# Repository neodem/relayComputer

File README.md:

# relayComputer
Files Relating to my Relay Based Computer

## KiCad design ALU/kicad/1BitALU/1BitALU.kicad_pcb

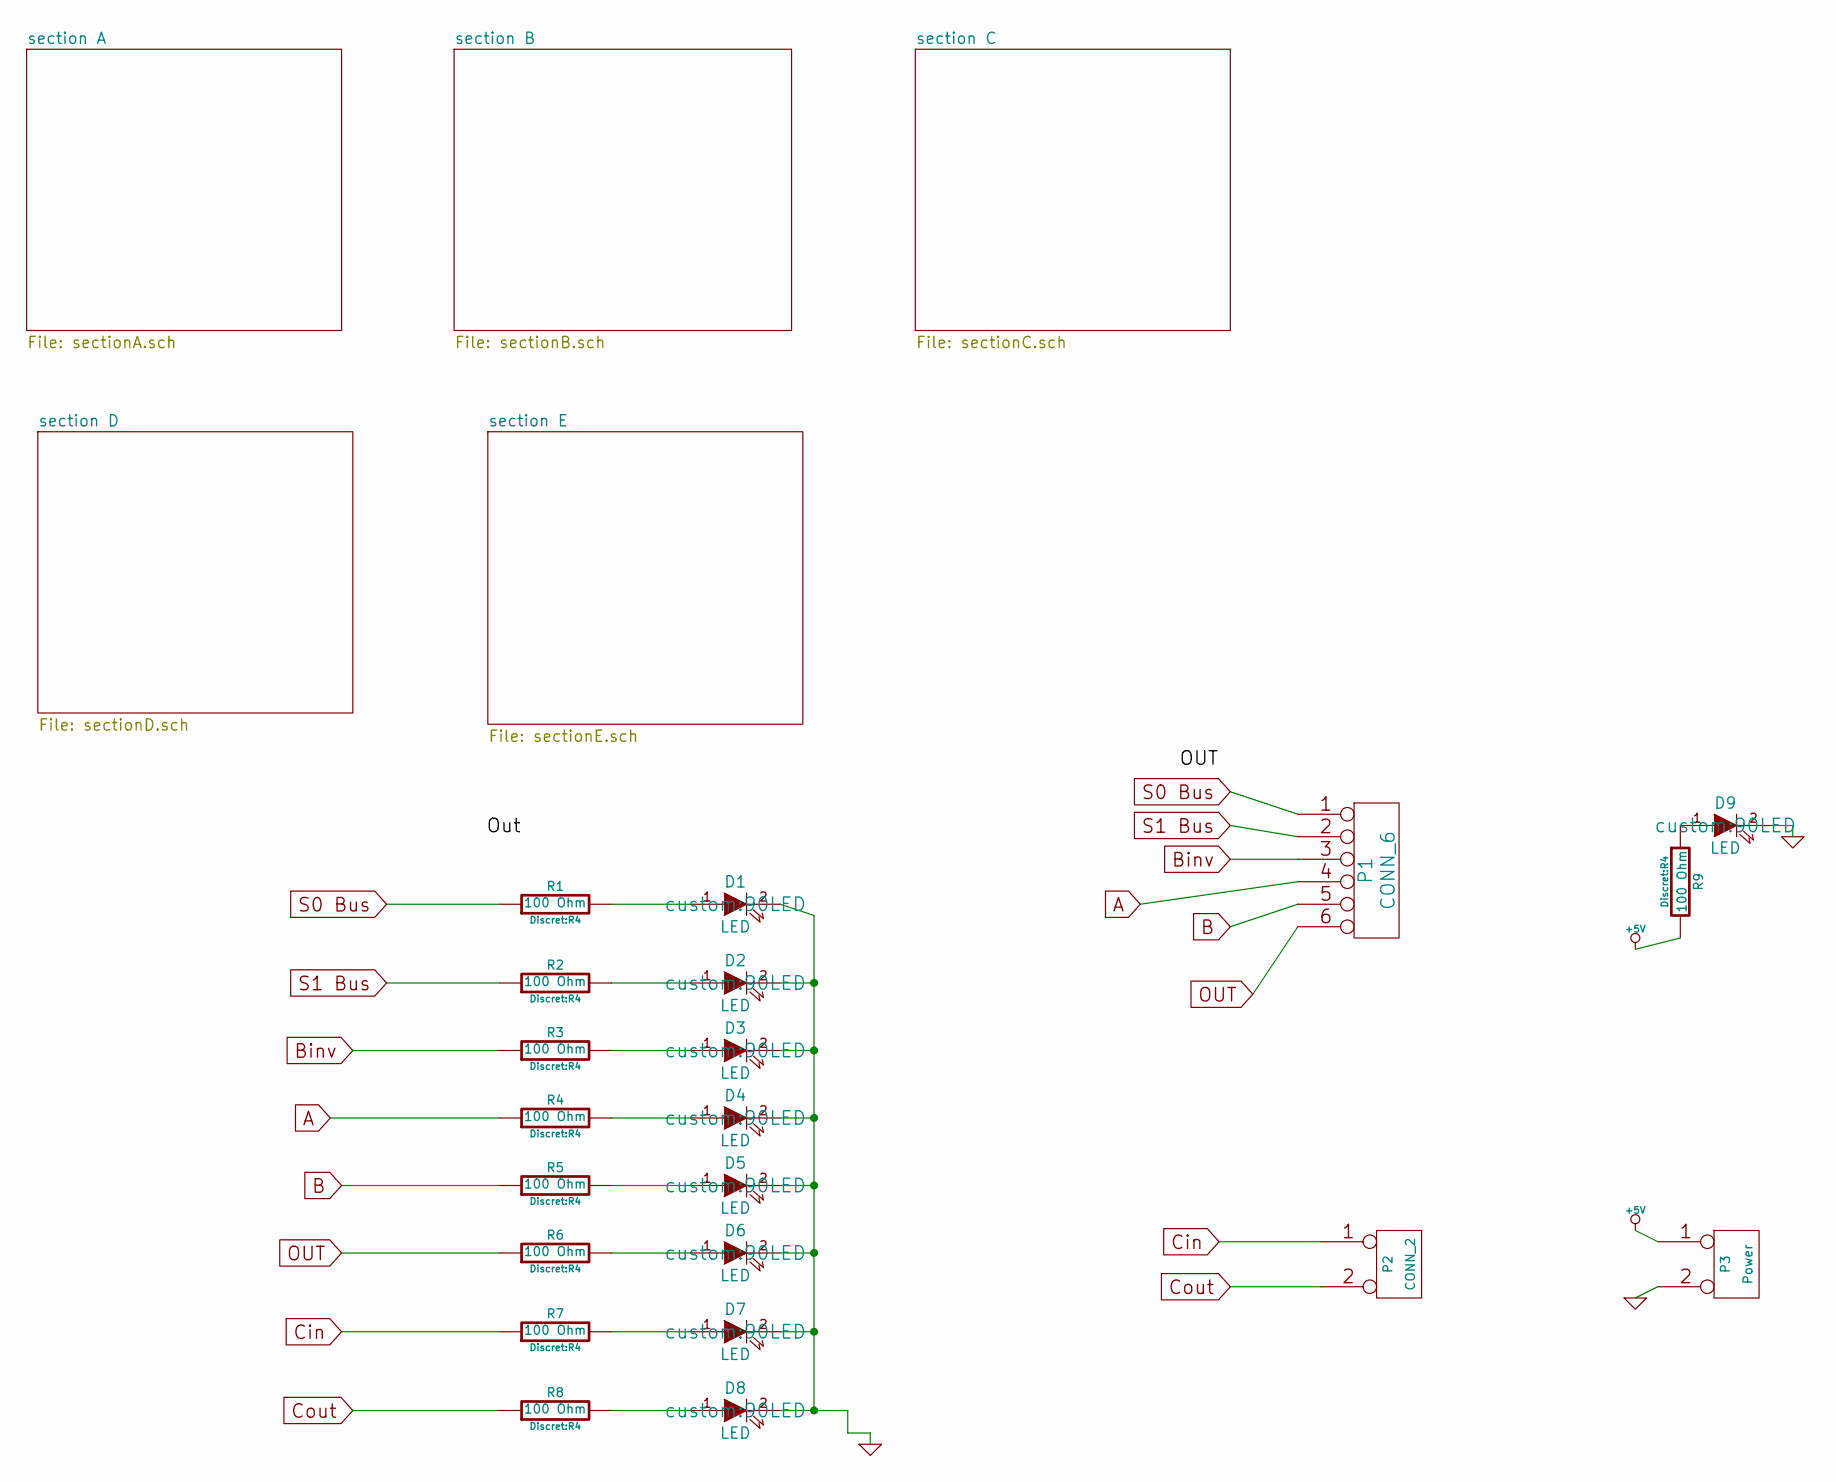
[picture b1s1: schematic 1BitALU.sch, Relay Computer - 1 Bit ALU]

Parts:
D1, D2, D3, D4, D5, D6, D7, D8, D9: LED; 90LED
P1: CONN_6; Socket_Strip_Angled_1x06
P2: CONN_2; Socket_Strip_Angled_1x02
P3: Power; Socket_Strip_Angled_1x02
R1, R2, R3, R4, R5, R6, R7, R8, R9: 100 Ohm; R4

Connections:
+5V: P3.1, R9.2; also elsewhere on the board
A: P1.4, R4.1; also elsewhere on the board
B: P1.5, R5.1; also elsewhere on the board
Binv: P1.3, R3.1; also elsewhere on the board
Cin: P2.1, R7.1; also elsewhere on the board
Cout: P2.2 (PM), R8.1; also elsewhere on the board
GND: D1.2 (K), D2.2 (K), D3.2 (K), D4.2 (K), D5.2 (K), D6.2 (K), D7.2 (K), D8.2 (K), D9.2 (K), P3.2 (PM); also elsewhere on the board
unnamed: D1.1 (A), R1.2
unnamed: D2.1 (A), R2.2
unnamed: D3.1 (A), R3.2
unnamed: D4.1 (A), R4.2
unnamed: D5.1 (A), R5.2
unnamed: D6.1 (A), R6.2
unnamed: D7.1 (A), R7.2
unnamed: D8.1 (A), R8.2
unnamed: D9.1 (A), R9.1
OUT: P1.6, R6.1; also elsewhere on the board
S0 Bus: P1.1, R1.1; also elsewhere on the board
S1 Bus: P1.2, R2.1; also elsewhere on the board

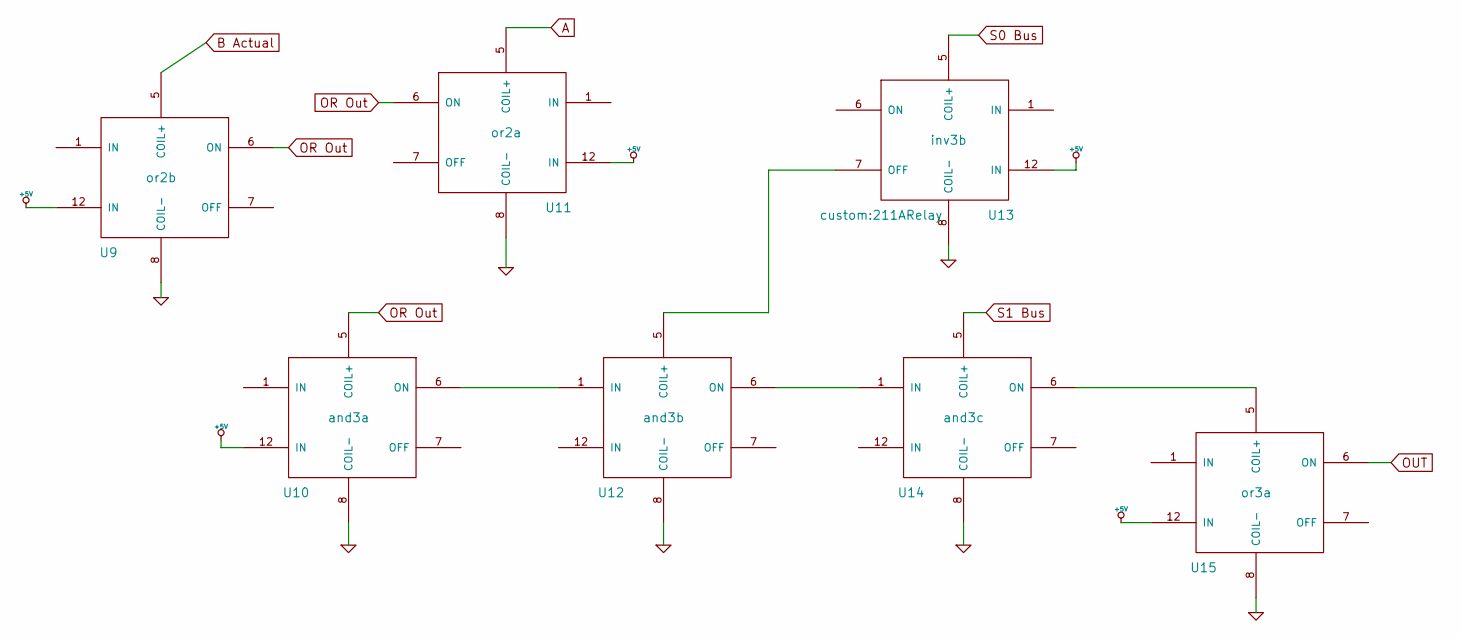
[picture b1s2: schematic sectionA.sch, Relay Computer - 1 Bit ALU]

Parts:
U9: or2b; 211ARelay
U10: and3a; 211ARelay
U11: or2a; 211ARelay
U12: and3b; 211ARelay
U13: inv3b; 211ARelay
U14: and3c; 211ARelay
U15: or3a; 211ARelay

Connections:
+5V: U9.12 (IN), U10.12 (IN), U11.12 (IN), U13.12 (IN), U15.12 (IN); also elsewhere on the board
A: U11.5 (COIL+); also elsewhere on the board
B Actual: U9.5 (COIL+); also elsewhere on the board
GND: U9.8 (COIL-), U10.8 (COIL-), U11.8 (COIL-), U12.8 (COIL-), U13.8 (COIL-), U14.8 (COIL-), U15.8 (COIL-); also elsewhere on the board
unnamed: U10.6 (ON), U12.1 (IN)
unnamed: U12.5 (COIL+), U13.7 (OFF)
unnamed: U12.6 (ON), U14.1 (IN)
unnamed: U14.6 (ON), U15.5 (COIL+)
OR Out: U9.6 (ON), U10.5 (COIL+), U11.6 (ON)
OUT: U15.6 (ON); also elsewhere on the board
S0 Bus: U13.5 (COIL+); also elsewhere on the board
S1 Bus: U14.5 (COIL+); also elsewhere on the board

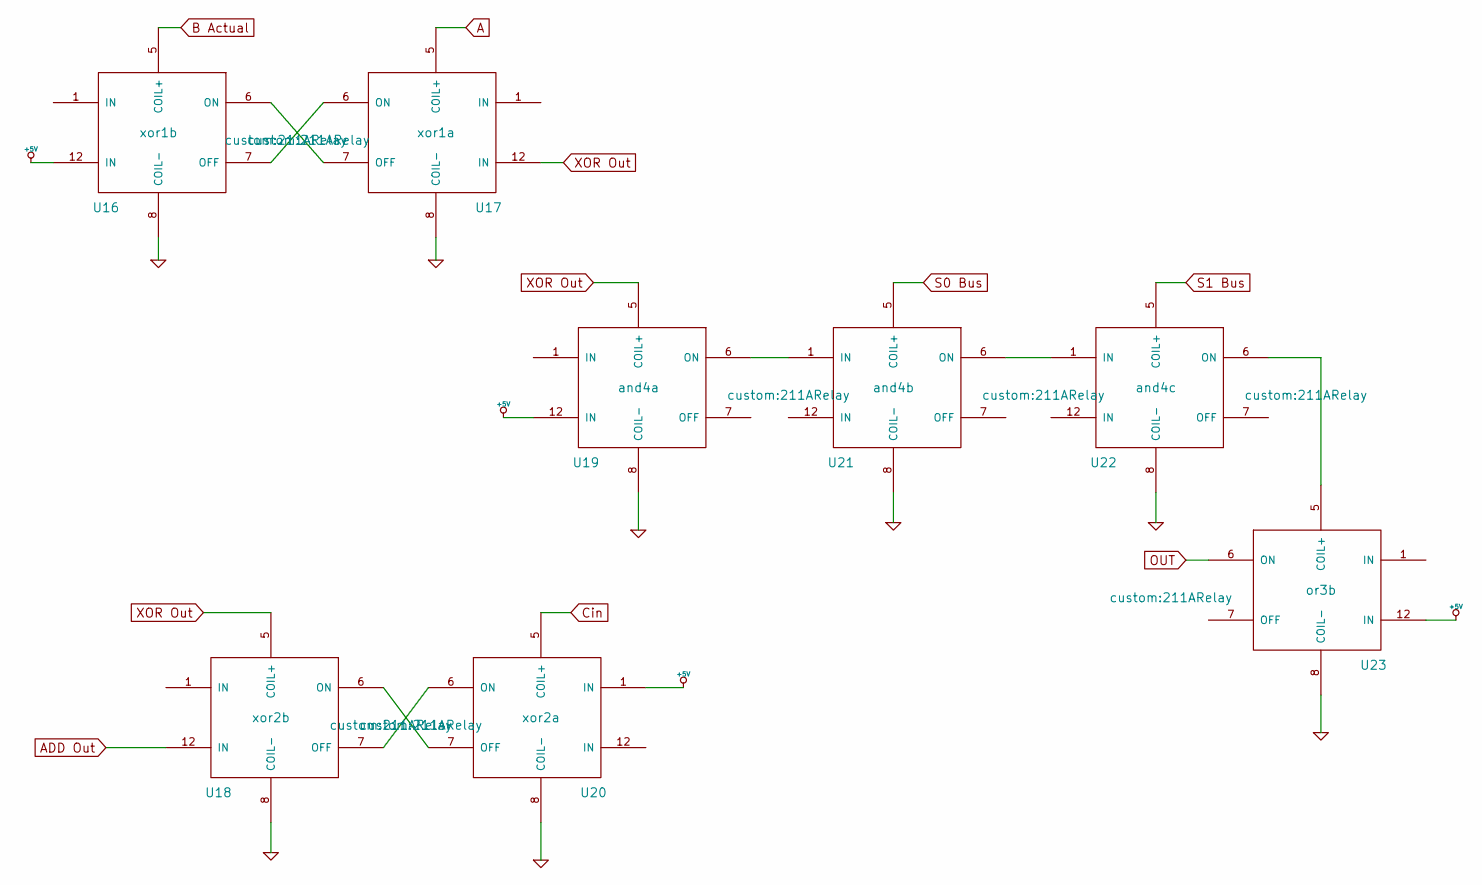
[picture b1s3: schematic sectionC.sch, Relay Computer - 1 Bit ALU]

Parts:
U16: xor1b; 211ARelay
U17: xor1a; 211ARelay
U18: xor2b; 211ARelay
U19: and4a; 211ARelay
U20: xor2a; 211ARelay
U21: and4b; 211ARelay
U22: and4c; 211ARelay
U23: or3b; 211ARelay

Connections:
+5V: U16.12 (IN), U19.12 (IN), U20.1 (IN), U23.12 (IN); also elsewhere on the board
A: U17.5 (COIL+); also elsewhere on the board
ADD Out: U18.12 (IN); also elsewhere on the board
B Actual: U16.5 (COIL+); also elsewhere on the board
Cin: U20.5 (COIL+); also elsewhere on the board
GND: U16.8 (COIL-), U17.8 (COIL-), U18.8 (COIL-), U19.8 (COIL-), U20.8 (COIL-), U21.8 (COIL-), U22.8 (COIL-), U23.8 (COIL-); also elsewhere on the board
unnamed: U16.6 (ON), U17.7 (OFF)
unnamed: U16.7 (OFF), U17.6 (ON)
unnamed: U18.6 (ON), U20.7 (OFF)
unnamed: U18.7 (OFF), U20.6 (ON)
unnamed: U19.6 (ON), U21.1 (IN)
unnamed: U21.6 (ON), U22.1 (IN)
unnamed: U22.6 (ON), U23.5 (COIL+)
OUT: U23.6 (ON); also elsewhere on the board
S0 Bus: U21.5 (COIL+); also elsewhere on the board
S1 Bus: U22.5 (COIL+); also elsewhere on the board
XOR Out: U17.12 (IN), U18.5 (COIL+), U19.5 (COIL+); also elsewhere on the board

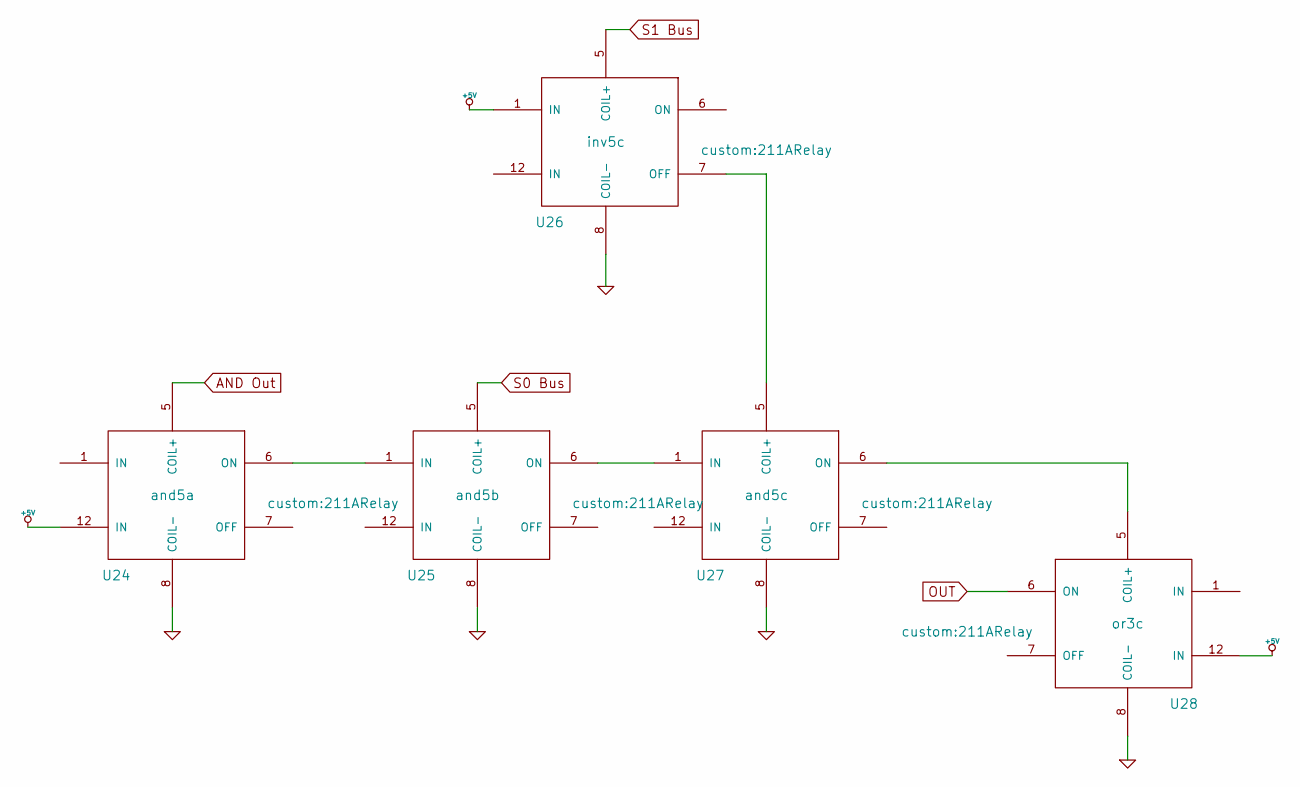
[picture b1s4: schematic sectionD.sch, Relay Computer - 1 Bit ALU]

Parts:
U24: and5a; 211ARelay
U25: and5b; 211ARelay
U26: inv5c; 211ARelay
U27: and5c; 211ARelay
U28: or3c; 211ARelay

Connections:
+5V: U24.12 (IN), U26.1 (IN), U28.12 (IN); also elsewhere on the board
AND Out: U24.5 (COIL+); also elsewhere on the board
GND: U24.8 (COIL-), U25.8 (COIL-), U26.8 (COIL-), U27.8 (COIL-), U28.8 (COIL-); also elsewhere on the board
unnamed: U24.6 (ON), U25.1 (IN)
unnamed: U25.6 (ON), U27.1 (IN)
unnamed: U26.7 (OFF), U27.5 (COIL+)
unnamed: U27.6 (ON), U28.5 (COIL+)
OUT: U28.6 (ON); also elsewhere on the board
S0 Bus: U25.5 (COIL+); also elsewhere on the board
S1 Bus: U26.5 (COIL+); also elsewhere on the board

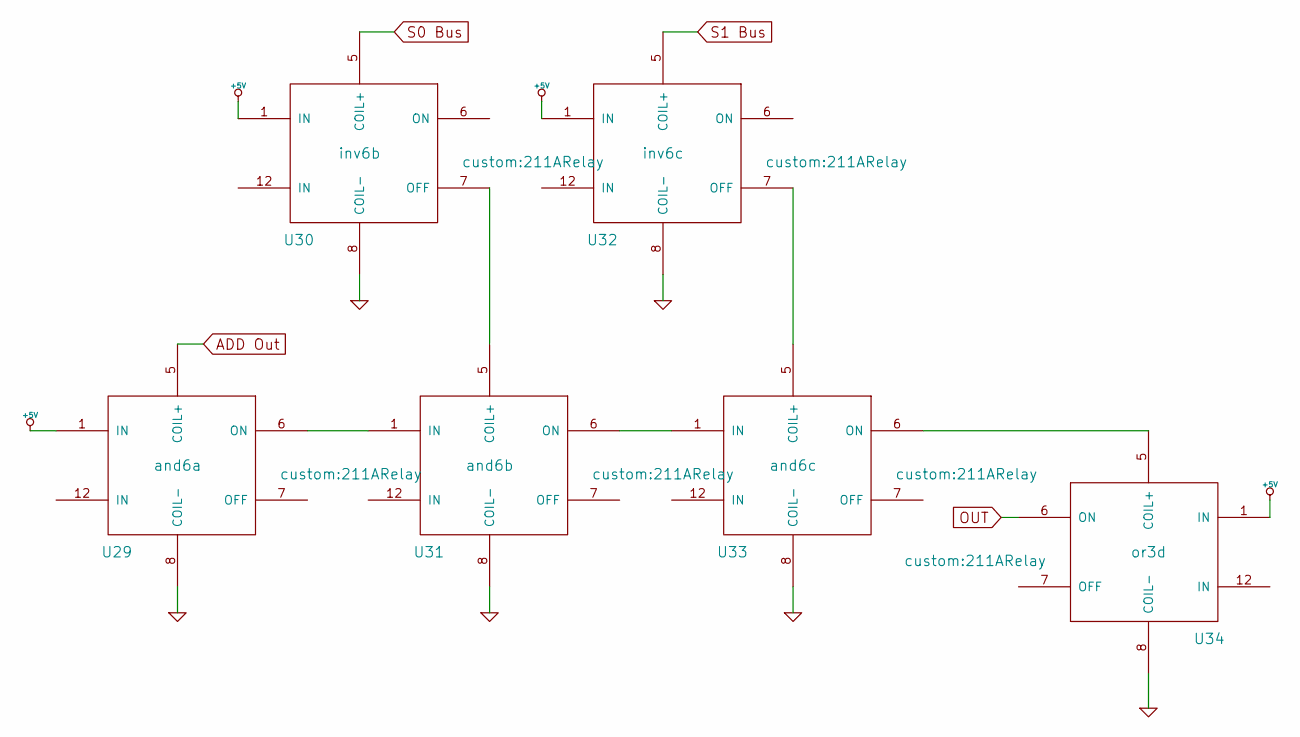
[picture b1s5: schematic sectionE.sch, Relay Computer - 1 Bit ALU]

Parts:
U29: and6a; 211ARelay
U30: inv6b; 211ARelay
U31: and6b; 211ARelay
U32: inv6c; 211ARelay
U33: and6c; 211ARelay
U34: or3d; 211ARelay

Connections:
+5V: U29.1 (IN), U30.1 (IN), U32.1 (IN), U34.1 (IN); also elsewhere on the board
ADD Out: U29.5 (COIL+); also elsewhere on the board
GND: U29.8 (COIL-), U30.8 (COIL-), U31.8 (COIL-), U32.8 (COIL-), U33.8 (COIL-), U34.8 (COIL-); also elsewhere on the board
unnamed: U29.6 (ON), U31.1 (IN)
unnamed: U30.7 (OFF), U31.5 (COIL+)
unnamed: U31.6 (ON), U33.1 (IN)
unnamed: U32.7 (OFF), U33.5 (COIL+)
unnamed: U33.6 (ON), U34.5 (COIL+)
OUT: U34.6 (ON); also elsewhere on the board
S0 Bus: U30.5 (COIL+); also elsewhere on the board
S1 Bus: U32.5 (COIL+); also elsewhere on the board

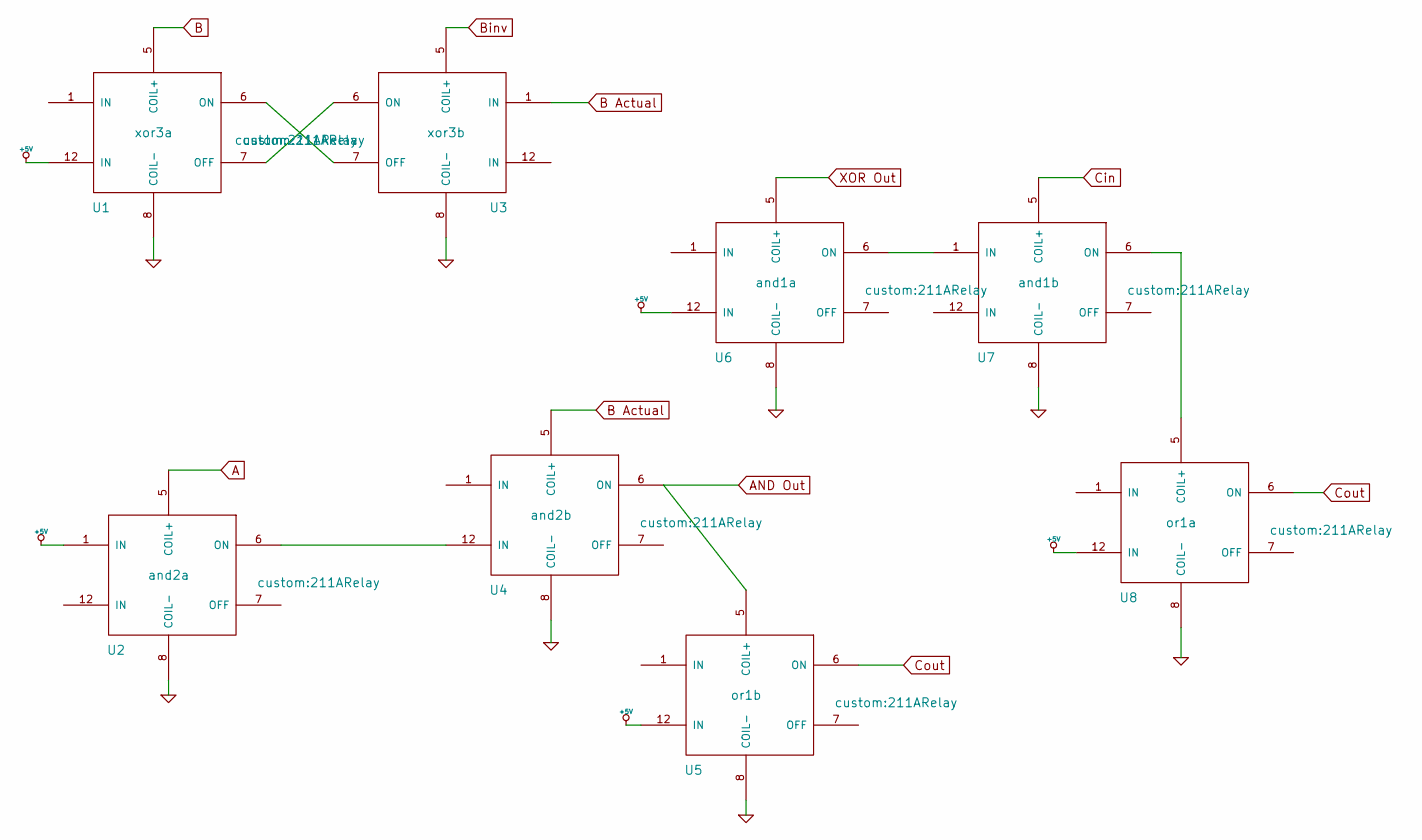
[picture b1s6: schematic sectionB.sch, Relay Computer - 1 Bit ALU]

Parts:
U1: xor3a; 211ARelay
U2: and2a; 211ARelay
U3: xor3b; 211ARelay
U4: and2b; 211ARelay
U5: or1b; 211ARelay
U6: and1a; 211ARelay
U7: and1b; 211ARelay
U8: or1a; 211ARelay

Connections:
+5V: U1.12 (IN), U2.1 (IN), U5.12 (IN), U6.12 (IN), U8.12 (IN); also elsewhere on the board
A: U2.5 (COIL+); also elsewhere on the board
AND Out: U4.6 (ON), U5.5 (COIL+); also elsewhere on the board
B: U1.5 (COIL+); also elsewhere on the board
B Actual: U3.1 (IN), U4.5 (COIL+); also elsewhere on the board
Binv: U3.5 (COIL+); also elsewhere on the board
Cin: U7.5 (COIL+); also elsewhere on the board
Cout: U5.6 (ON), U8.6 (ON); also elsewhere on the board
GND: U1.8 (COIL-), U2.8 (COIL-), U3.8 (COIL-), U4.8 (COIL-), U5.8 (COIL-), U6.8 (COIL-), U7.8 (COIL-), U8.8 (COIL-); also elsewhere on the board
unnamed: U1.6 (ON), U3.7 (OFF)
unnamed: U1.7 (OFF), U3.6 (ON)
unnamed: U2.6 (ON), U4.12 (IN)
unnamed: U6.6 (ON), U7.1 (IN)
unnamed: U7.6 (ON), U8.5 (COIL+)
XOR Out: U6.5 (COIL+); also elsewhere on the board

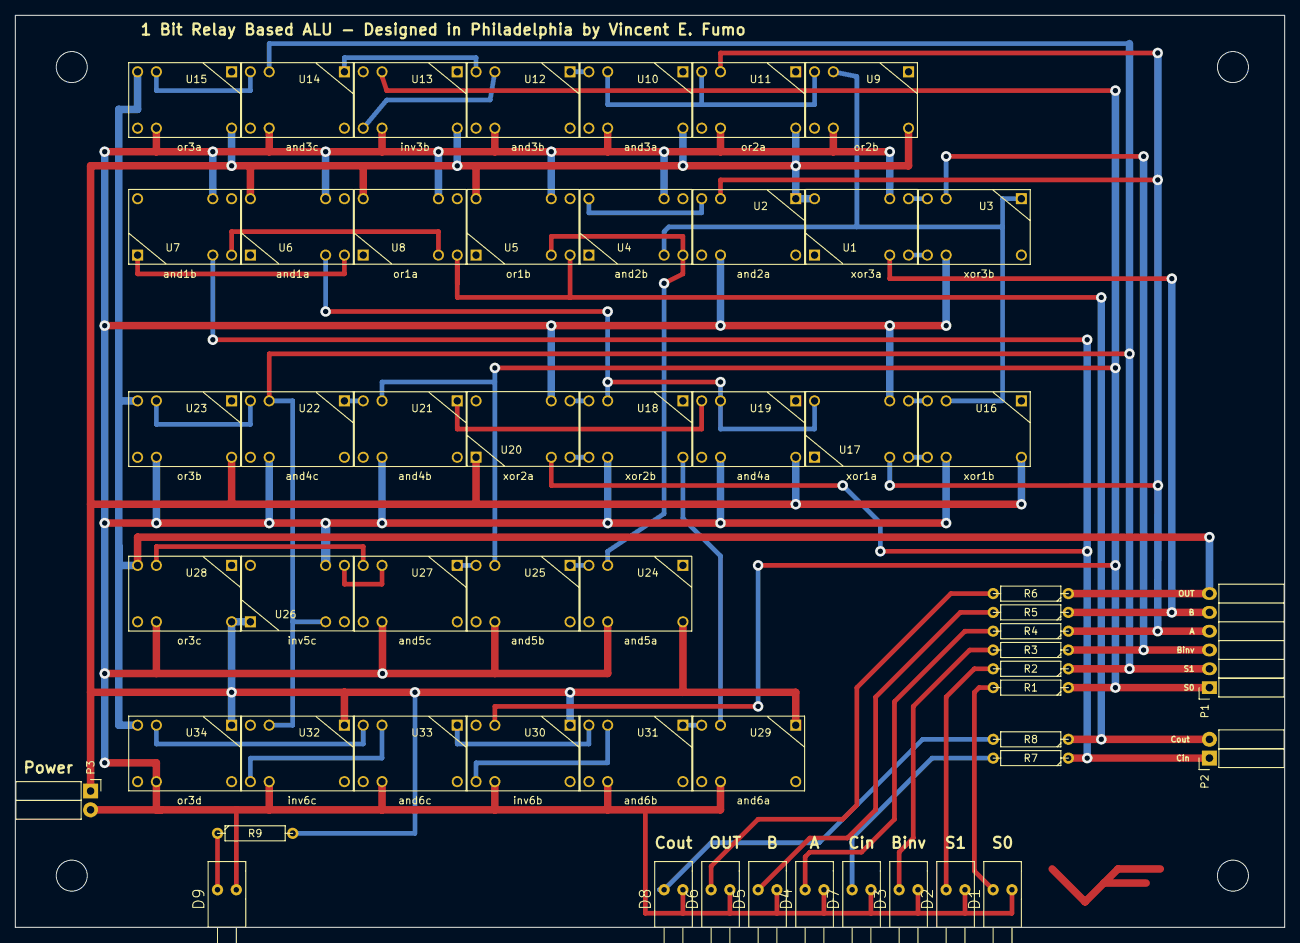
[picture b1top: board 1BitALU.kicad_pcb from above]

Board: 2 copper layers, 171.5 x 123.2 mm, 55 parts (0 on the bottom side), 49 nets.

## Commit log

2015-03-10 * improvements
2015-03-10 test
2015-03-10 adds schematic and functional PDFs
2015-03-27 more updates
2015-04-05 interim version
2015-04-05 puts bus connectors on side
2015-04-05 cleanup
2015-04-05 adds gerbers
2015-04-25 bigger drill holes
